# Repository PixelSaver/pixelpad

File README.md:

# PixelPad

PixelPad is a 5 key macropad with a rotary encoder, an OLED screen, and two LEDs. It's my first piece of hardware I've ever made (I don't count building a pc), so I'm really excited to use seomthing made by me. I tried to make it as compact as possible while still fitting everything.

It was made for the Hackclub organization's Hackpad YSWS. I took major inspiration from the example [OrpheusPad](https://github.com/hackclub/hackpad/blob/main/hackpads/orpheuspad), so check that project out too! 

## Features
- 128x32 OLED Display
- EC11 Rotary encoder for (probably) Volume
- 2 WS2812B RGB LEDs. Both are at the top right to signify the mode / power / whatever other info is needed
- 5 Keys
- Hopefully VIA Support!

## Cad Model

Everything bolts together using 5 M3 bolts (one of the bolts isn't 16, its 12 which will need some cutting once it gets shipped). The bottom of the case makes a 5 degree tilt so that the screen is easier read. 

Printed in 4 separate pieces, the bottom case, the switch plate in the middle, the top cover, and a knob.

Made in OnShape!! Screw Fusion360 and their predatory pricing tactics!

## PCB

Made using KiCad, here's the pcb and schematics for everything.
### PCB

### Schematic

## Firmware

The macropad uses QMK for its firmware. I still haven't wrapped my head around how that works, and I plan to tinker once I build it. 

For now, I can pray that the features are there, and that I can run some code for the OLED for a clock or music playing.

## Materials

- 5x Cherry MX Switches
- 5x DSA Keycaps
- 5x M3x5x4 Heatset inserts
- 4x M3x16mm SHCS Bolts
- 1X M3x12mm SHCS Bolts
- 6x 1N4148 DO-35 Diodes.
- 2x WS2812B LEDs
- 1x 0.91" 128x32 OLED Display
- 1x EC11 Rotary Encoder
- 1x XIAO RP2040
- 1x Case (3 printed parts)
- 1x Knob (Printed)

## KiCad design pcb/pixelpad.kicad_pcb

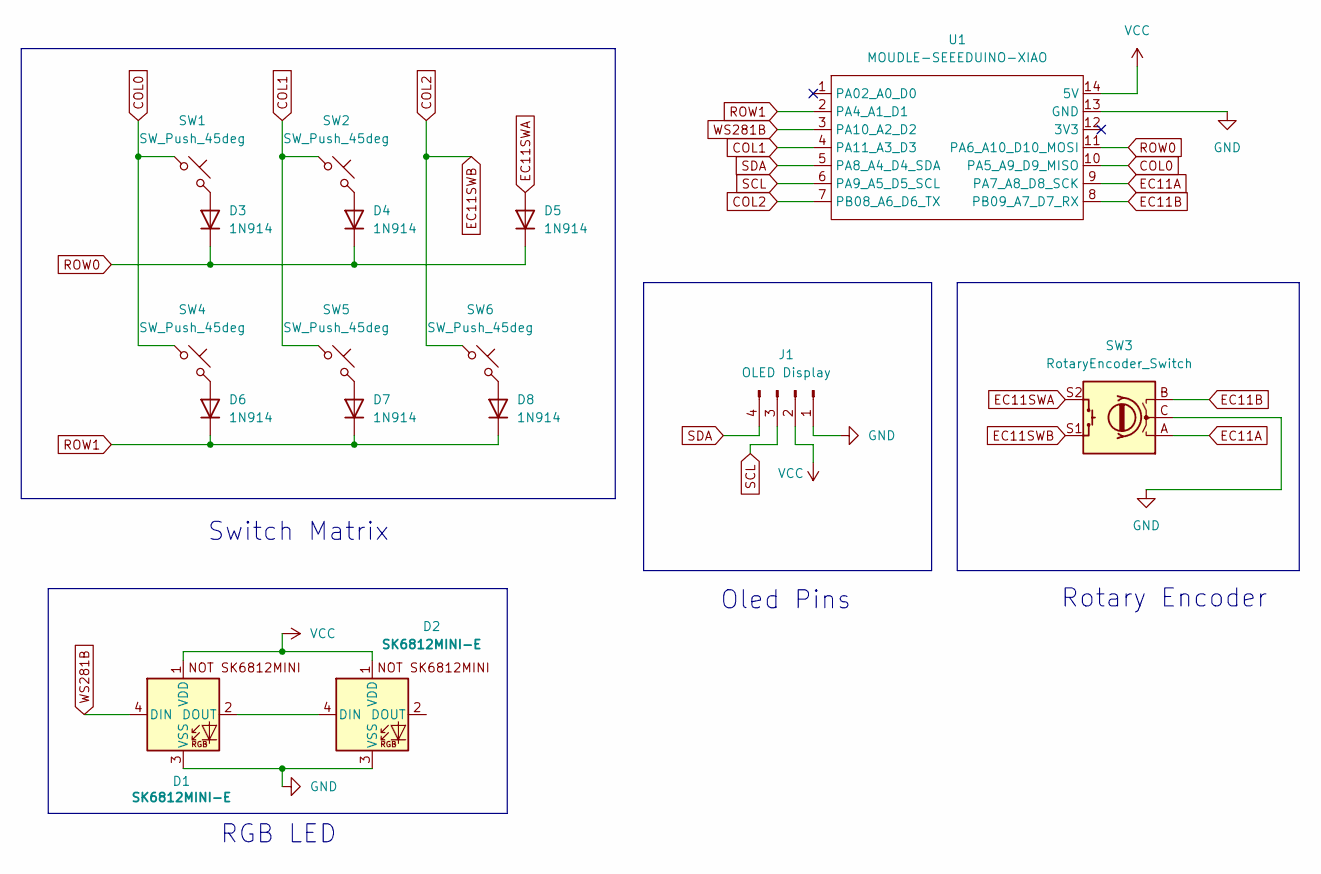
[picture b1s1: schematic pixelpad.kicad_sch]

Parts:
D1, D2: SK6812MINI-E; SK6812MINI-E_fixed
D3, D4, D5, D6, D7, D8: 1N914; D_DO-35_SOD27_P7.62mm_Horizontal
J1: OLED Display; PinHeader_1x04_P2.54mm_Vertical
SW1, SW2, SW4, SW5, SW6: SW_Push_45deg; SW_Cherry_MX_1.00u_PCB
SW3: RotaryEncoder_Switch; RotaryEncoder_Alps_EC11E-Switch_Vertical_H20mm
U1: MOUDLE-SEEEDUINO-XIAO; XIAO-Generic-Hybrid-14P-2.54-21X17.8MM

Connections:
COL0: SW1.1, SW4.1, U1.10 (PA5_A9_D9_MISO)
COL1: SW2.1, SW5.1, U1.4 (PA11_A3_D3)
COL2: SW3.S1, SW6.1, U1.7 (PB08_A6_D6_TX)
EC11A: SW3.A, U1.9 (PA7_A8_D8_SCK)
EC11B: SW3.B, U1.8 (PB09_A7_D7_RX)
EC11SWA: D5.2 (A), SW3.S2
GND: D1.3 (VSS), D2.3 (VSS), J1.1, SW3.C, U1.13 (GND)
unnamed: D1.2 (DOUT), D2.4 (DIN)
unnamed: D3.2 (A), SW1.2
unnamed: D4.2 (A), SW2.2
unnamed: D6.2 (A), SW4.2
unnamed: D7.2 (A), SW5.2
unnamed: D8.2 (A), SW6.2
ROW0: D3.1 (K), D4.1 (K), D5.1 (K), U1.11 (PA6_A10_D10_MOSI)
ROW1: D6.1 (K), D7.1 (K), D8.1 (K), U1.2 (PA4_A1_D1)
SCL: J1.3, U1.6 (PA9_A5_D5_SCL)
SDA: J1.4, U1.5 (PA8_A4_D4_SDA)
VCC: D1.1 (VDD), D2.1 (VDD), J1.2, U1.14 (5V)
WS281B: D1.4 (DIN), U1.3 (PA10_A2_D2)

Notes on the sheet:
Rotary Encoder
RGB LED
Oled Pins
Switch Matrix

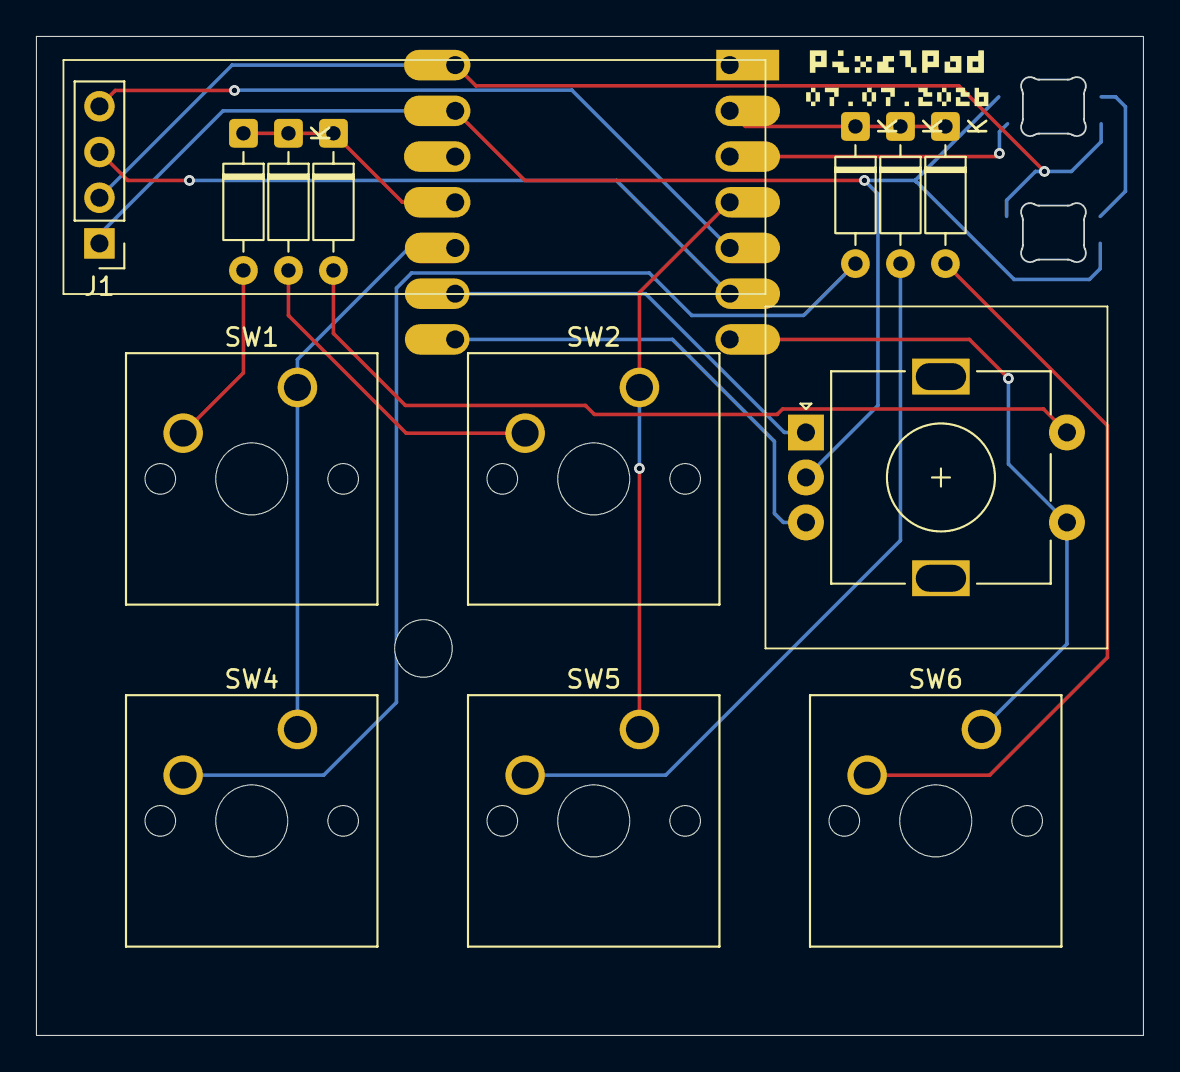
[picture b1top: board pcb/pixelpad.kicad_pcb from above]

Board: 2 copper layers, 61.5 x 55.5 mm, 16 parts (1 on the bottom side), 19 nets.

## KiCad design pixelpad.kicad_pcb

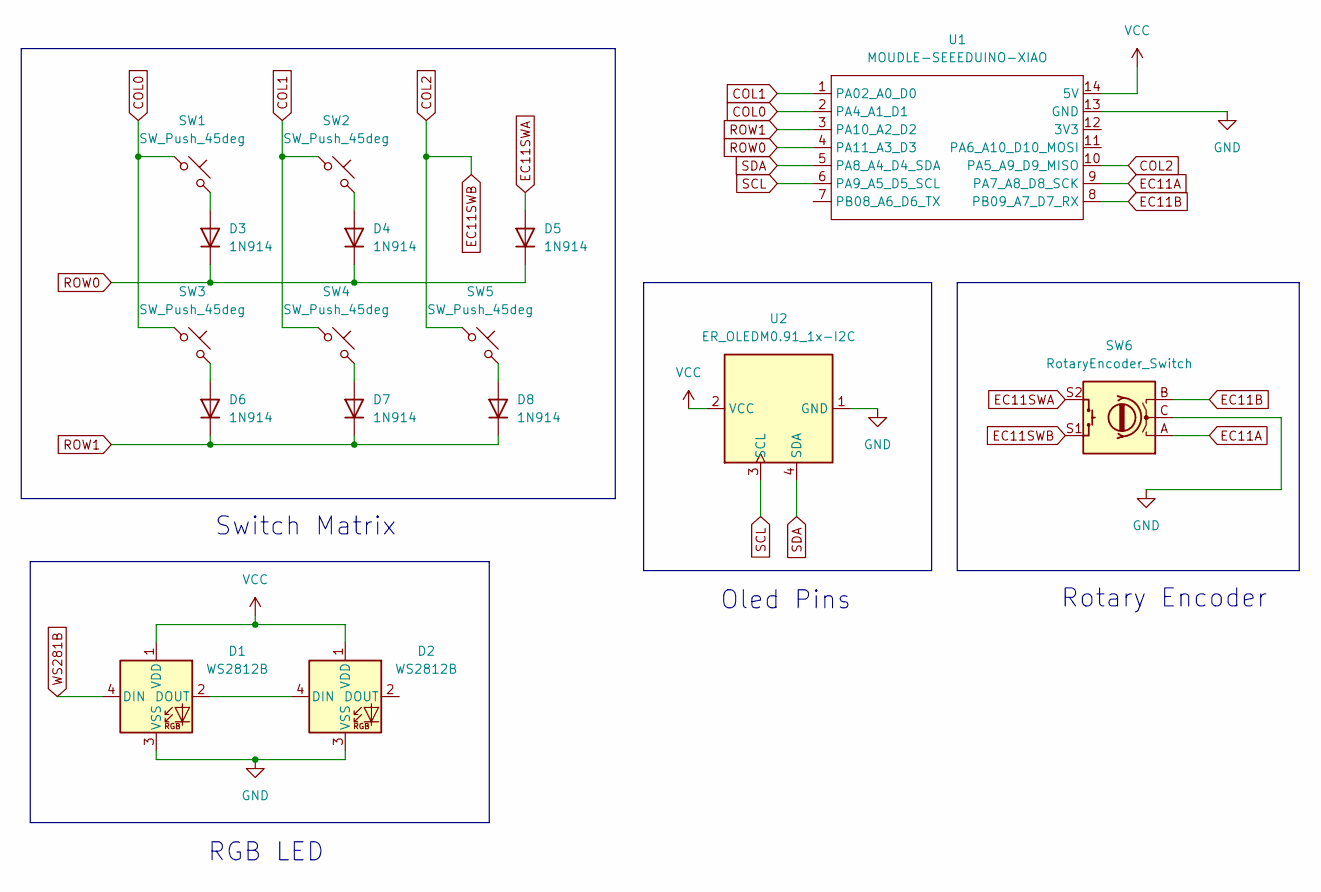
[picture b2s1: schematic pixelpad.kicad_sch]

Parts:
D1, D2: WS2812B; LED_WS2812B_PLCC4_5.0x5.0mm_P3.2mm
D3, D4, D5, D6, D7, D8: 1N914; D_DO-35_SOD27_P7.62mm_Horizontal
SW1, SW2, SW3, SW4, SW5: SW_Push_45deg; SW_Cherry_MX_1.00u_PCB
SW6: RotaryEncoder_Switch; RotaryEncoder_Alps_EC11E-Switch_Vertical_H20mm
U1: MOUDLE-SEEEDUINO-XIAO; XIAO-Generic-Hybrid-14P-2.54-21X17.8MM
U2: ER_OLEDM0.91_1x-I2C

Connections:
COL0: SW1.1, SW3.1, U1.2 (PA4_A1_D1)
COL1: SW2.1, SW4.1, U1.1 (PA02_A0_D0)
COL2: SW5.1, SW6.S1, U1.10 (PA5_A9_D9_MISO)
EC11A: SW6.A, U1.9 (PA7_A8_D8_SCK)
EC11B: SW6.B, U1.8 (PB09_A7_D7_RX)
EC11SWA: D5.2 (A), SW6.S2
GND: D1.3 (VSS), D2.3 (VSS), SW6.C, U1.13 (GND), U2.1 (GND)
unnamed: D1.2 (DOUT), D2.4 (DIN)
unnamed: D3.2 (A), SW1.2
unnamed: D4.2 (A), SW2.2
unnamed: D6.2 (A), SW3.2
unnamed: D7.2 (A), SW4.2
unnamed: D8.2 (A), SW5.2
ROW0: D3.1 (K), D4.1 (K), D5.1 (K), U1.4 (PA11_A3_D3)
ROW1: D6.1 (K), D7.1 (K), D8.1 (K), U1.3 (PA10_A2_D2)
SCL: U1.6 (PA9_A5_D5_SCL), U2.3 (SCL)
SDA: U1.5 (PA8_A4_D4_SDA), U2.4 (SDA)
VCC: D1.1 (VDD), D2.1 (VDD), U1.14 (5V), U2.2 (VCC)
WS281B: D1.4 (DIN)

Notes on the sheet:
Rotary Encoder
RGB LED
Oled Pins
Switch Matrix

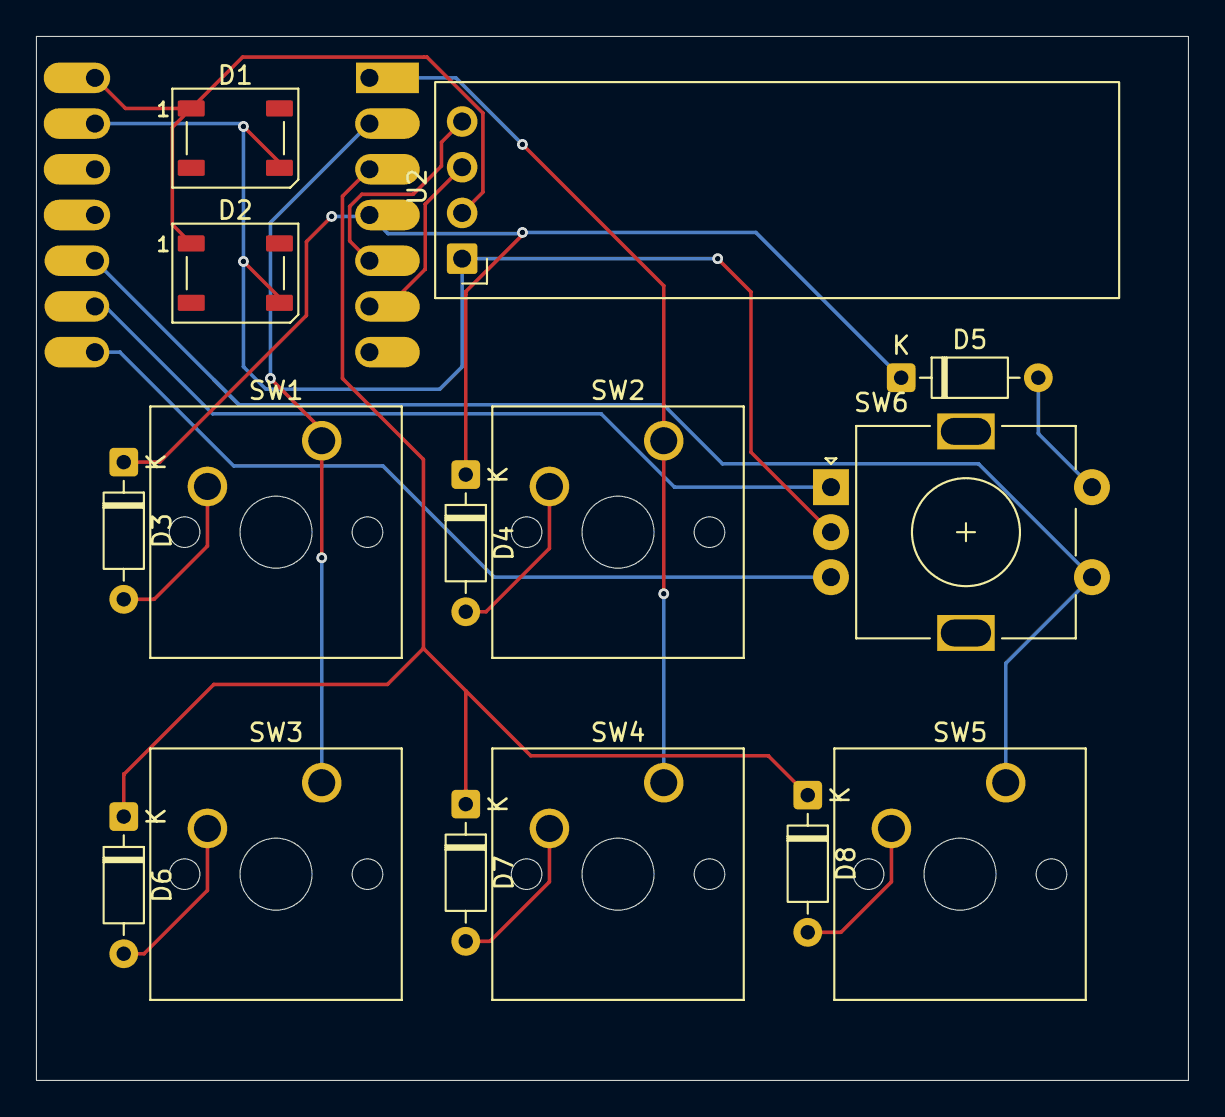
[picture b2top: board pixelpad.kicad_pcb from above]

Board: 2 copper layers, 64.0 x 58.0 mm, 16 parts (1 on the bottom side), 18 nets.

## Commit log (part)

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2026-06-29 New project
2026-06-29 Finished PCB
2026-06-29 Added case file
